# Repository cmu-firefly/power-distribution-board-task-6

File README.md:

View this project on [CADLAB.io](https://cadlab.io/project/25207). 

# power-distribution-board-task-6

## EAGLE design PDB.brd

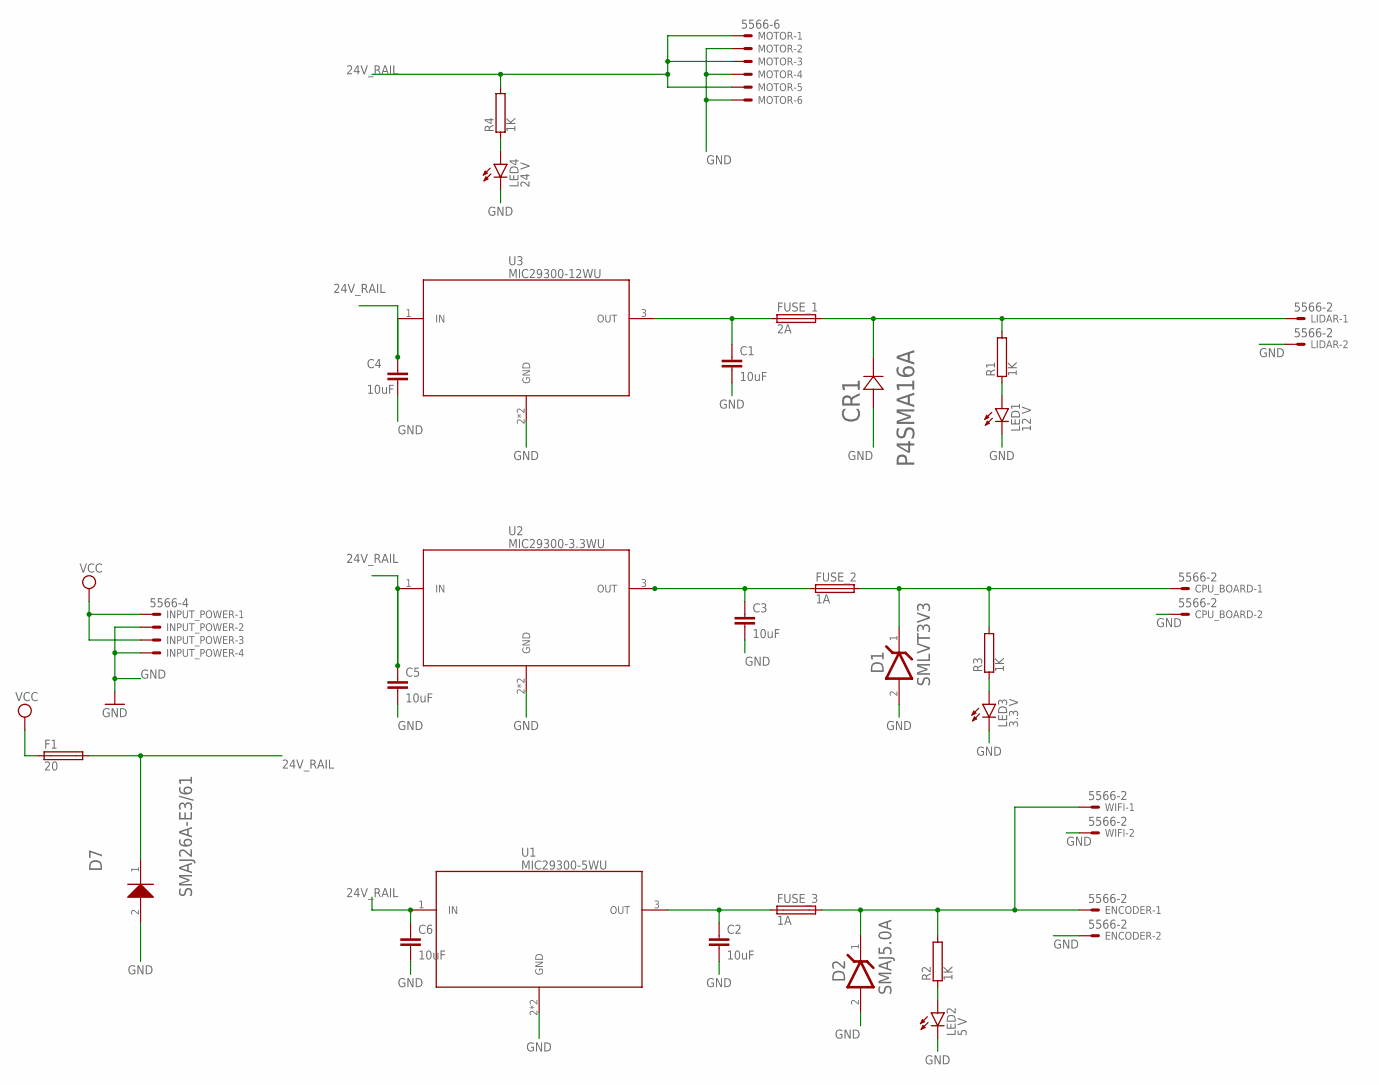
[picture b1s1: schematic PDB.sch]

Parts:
C1, C2, C3, C4, C5, C6: 10uF; C2.5-2
CPU_BOARD: 5566-2
CR1: P4SMA16A; P4SMASERIES_LTF
D1: STMICROELECTRONICS_SMLVT3V3STMICROELECTRONICS_SML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; STMICROELECTRONICS_SMLVT3V3_0
D2: LITTELFUSE_INC._SMAJ5.0ALITTELFUSE_INC._SMAJ5.0A_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; LITTELFUSE_INC._SMAJ5.0A_0
D7: VISHAY_SEMICONDUCTOR_SMAJ26A-E3-61VISHAY_SEMICOND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; VISHAY_SEMICONDUCTOR_SMAJ26A-E3-61_0
ENCODER: 5566-2
F1: 20; TE5
FUSE_1: 2A; TE5
FUSE_2, FUSE_3: 1A; TE5
INPUT_POWER: 5566-4
LED1: 12 V; CHIPLED_0805
LED2: 5 V; CHIPLED_0805
LED3: 3.3 V; CHIPLED_0805
LED4: 24 V; CHIPLED_0805
LIDAR: 5566-2
MOTOR: 5566-6
R1, R2, R3, R4: 1K; TO-247-2V
U1: MIC29300-5WU; TO263
U2: MIC29300-3.3WU; TO263
U3: MIC29300-12WU; TO263
WIFI: 5566-2

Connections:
24V_RAIL: C4.1, C5.1, C6.1, D7.1 (K), F1.2, MOTOR.1, MOTOR.3, MOTOR.5, R4.2, U1.1 (IN), U2.1 (IN), U3.1 (IN)
GND: C1.2, C2.2, C3.2, C4.2, C5.2, C6.2, CPU_BOARD.2, CR1.2 (12), D1.2 (A), D2.2 (ANODE), D7.2 (A), ENCODER.2, INPUT_POWER.2, INPUT_POWER.4, LED1.C, LED2.C, LED3.C, LED4.C, LIDAR.2, MOTOR.2, MOTOR.4, MOTOR.6, U1.2 (GND), U1.GND@ (GND), U2.2 (GND), U2.GND@ (GND), U3.2 (GND), U3.GND@ (GND), WIFI.2
unnamed: C1.1, FUSE_1.1, U3.3 (OUT)
unnamed: LED4.A, R4.1
unnamed: C2.1, FUSE_3.1, U1.3 (OUT)
unnamed: C3.1, FUSE_2.1, U2.3 (OUT)
unnamed: CPU_BOARD.1, D1.1 (K), FUSE_2.2, R3.2
unnamed: D2.1 (CATHODE), ENCODER.1, FUSE_3.2, R2.2, WIFI.1
unnamed: CR1.1 (11), FUSE_1.2, LIDAR.1, R1.2
unnamed: LED1.A, R1.1
unnamed: LED3.A, R3.1
unnamed: LED2.A, R2.1
VCC: F1.1, INPUT_POWER.1, INPUT_POWER.3

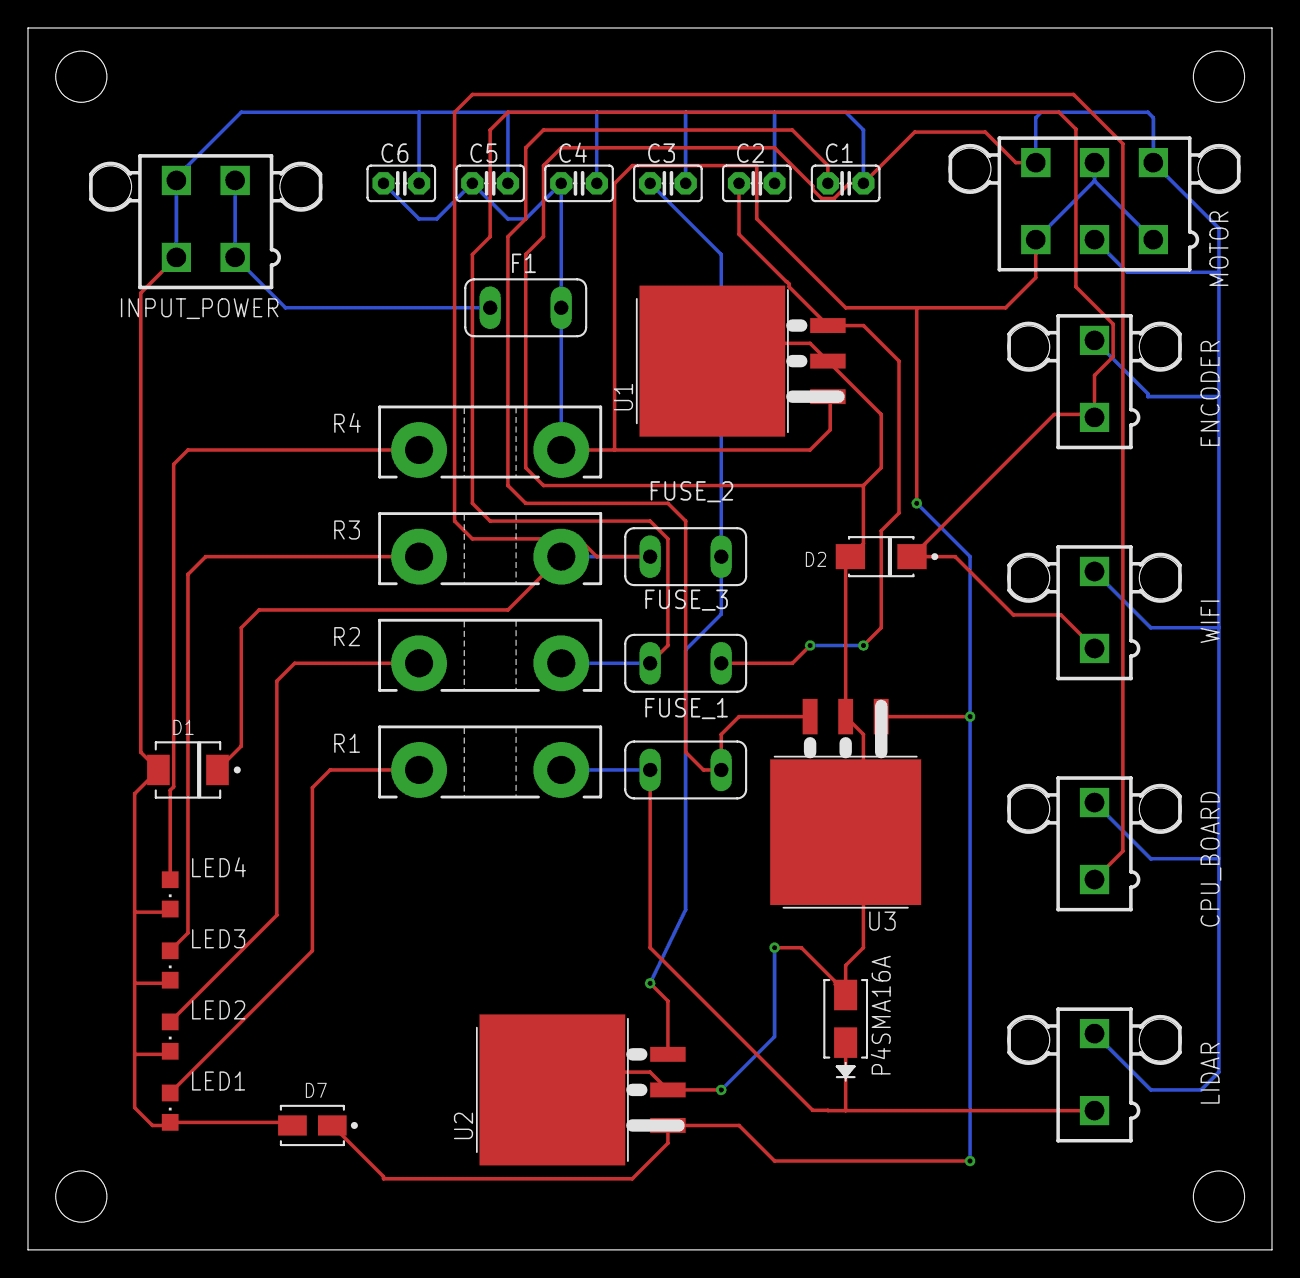
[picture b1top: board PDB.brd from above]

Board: 2 copper layers, 88.9 x 87.3 mm, 31 parts (0 on the bottom side), 13 nets.

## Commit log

2022-02-13 Added empty schematic file and made repo an Eagle project
2022-02-13 Backlink to CADLAB.io has been added.
2022-02-18 Schematic of PCB done
2022-02-18 Added board. DO NOT SUBMIT.
2022-02-18 updated components on board
2022-02-18 wiring complete
2022-02-18 Updated MIC2930 linear regulators to all use the same symbol and footprint. Fixed all warnings and errors with schematic and board.
2022-04-12 Add files via upload
    adding smaartwire reading. Arduino tested, ros wrapper untested.
2022-04-12 Add files via upload
    uploading SmaartWire Library. PCB Validation code in examples: arduino code is tested, ros code is untested.

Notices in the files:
parts and their libraries:
COPYRIGHT: Copyright (C) 2022 Ultra Librarian. All rights reserved.
